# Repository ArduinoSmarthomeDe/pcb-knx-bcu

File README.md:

# KNX TP-UART bus coupler module

## Description

Small KNX bus coupling module to connect microcontrollers like Arduino over the serial interface. Uses the first version of the Siemens TP-UART chip and is easy to handle by hand. Perfectly suited for small KNX self-made devices.

**Dimensions:** 19 x 34 mm

*This is just a DIY board, so there is no official KNX stack to configure via the ETS software.*

## Preview

A little look at the finished circuit board (3D model):

## Parts

Some parts are a hard to come by, so here is a short overview of known distributors (no affiliates).

| Item      | Part                    | Link  |
| --------- |:-----------------------:| ----- |
| U1        | Siemens TP-Uart         | http://www.opternus.com/de/siemens/knx-chipset/knx-transceiver-ics-tp-uart-fze1066.html |
| D2        | P4SMAJ43A               | https://www.reichelt.de/tvs-diode-unidirektional-43-v-400-w-do-214ac-sma-p4smaj43a-p272910.html?&trstct=pos_0&nbc=1 |
| D3        | RND US1M-AT             | https://www.reichelt.de/gleichrichterdiode-1000-v-1-a-do-214ac-sma-us-1m-p146618.html?&trstct=pos_0&nbc=1 |

## Layout & Production 

You can find all the open data here as a [KiCad](http://kicad.github.io) project. You can find all the necessary dependencies such as footprints or libraries in the folder **KiCad Symbols & Footprints**.

The *Gerber files* for the production of the board can be found here under **releases**.

## License

The MIT License (MIT)

Copyright (c) 2021 André Husken hello@arduino-smarthome.de

Permission is hereby granted, free of charge, to any person obtaining a copy of this software and associated documentation files (the "Software"), to deal in the Software without restriction, including without limitation the rights to use, copy, modify, merge, publish, distribute, sublicense, and/or sell copies of the Software, and to permit persons to whom the Software is furnished to do so, subject to the following conditions:

The above copyright notice and this permission notice shall be included in all copies or substantial portions of the Software.

THE SOFTWARE IS PROVIDED "AS IS", WITHOUT WARRANTY OF ANY KIND, EXPRESS OR IMPLIED, INCLUDING BUT NOT LIMITED TO THE WARRANTIES OF MERCHANTABILITY, FITNESS FOR A PARTICULAR PURPOSE AND NONINFRINGEMENT. IN NO EVENT SHALL THE AUTHORS OR COPYRIGHT HOLDERS BE LIABLE FOR ANY CLAIM, DAMAGES OR OTHER LIABILITY, WHETHER IN AN ACTION OF CONTRACT, TORT OR OTHERWISE, ARISING FROM, OUT OF OR IN CONNECTION WITH THE SOFTWARE OR THE USE OR OTHER DEALINGS IN THE SOFTWARE.

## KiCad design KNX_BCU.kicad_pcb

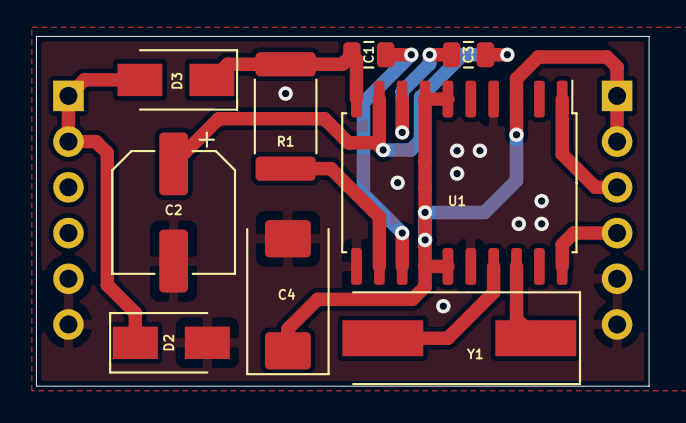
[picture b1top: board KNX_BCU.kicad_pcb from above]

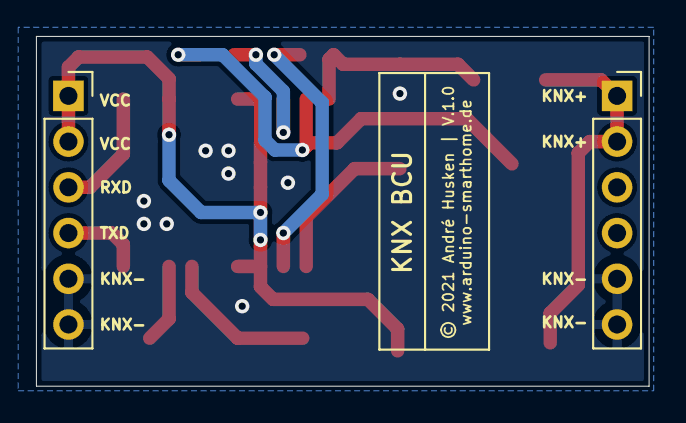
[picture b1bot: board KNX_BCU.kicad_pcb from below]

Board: 2 copper layers, 34.0 x 19.4 mm, 11 parts (2 on the bottom side), 12 nets.

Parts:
C1, C3: 47nF; C_0805_2012Metric
C2: 100uF/35V; CP_Elec_6.3x7.7
C4: T491D 6,8U 35; CP_EIA-7343-20_Kemet-V
D2: P4SMAJ43A; D_SMA
D3: RND US1M-AT; D_SMA
J1, J2: Conn_01x06_Female; PinSocket_1x06_P2.54mm_Vertical
R1: 68/1W; R_2512_6332Metric
U1: EIB-TP-UART; SOIC-20W_7.5x12.8mm_P1.27mm
Y1: 4.915MHz; Crystal_SMD_HC49-SD

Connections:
KNX+: D2.1, D3.2, J1.1, J1.2
KNX-: C2.2, C4.2, D2.2, J1.5, J1.6, J2.5, J2.6, U1.4, U1.11, U1.16
unnamed: C1.1, D3.1, R1.1, U1.10
unnamed: C1.2, U1.13
unnamed: C2.1, C3.1, U1.9
unnamed: C3.2, U1.8
unnamed: R1.2, U1.12
unnamed: U1.17, Y1.2
unnamed: U1.18, Y1.1
RXD: J2.3, U1.1
TXD: J2.4, U1.20
VCC: C4.1, J2.1, J2.2, U1.3, U1.6, U1.7, U1.14, U1.15

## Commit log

2021-09-08 readme, preview
2021-09-08 V.1.0
2021-09-08 readme
2021-09-08 preview

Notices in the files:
KNX_BCU.kicad_pcb:
© 2021 André Husken | V.1.0
